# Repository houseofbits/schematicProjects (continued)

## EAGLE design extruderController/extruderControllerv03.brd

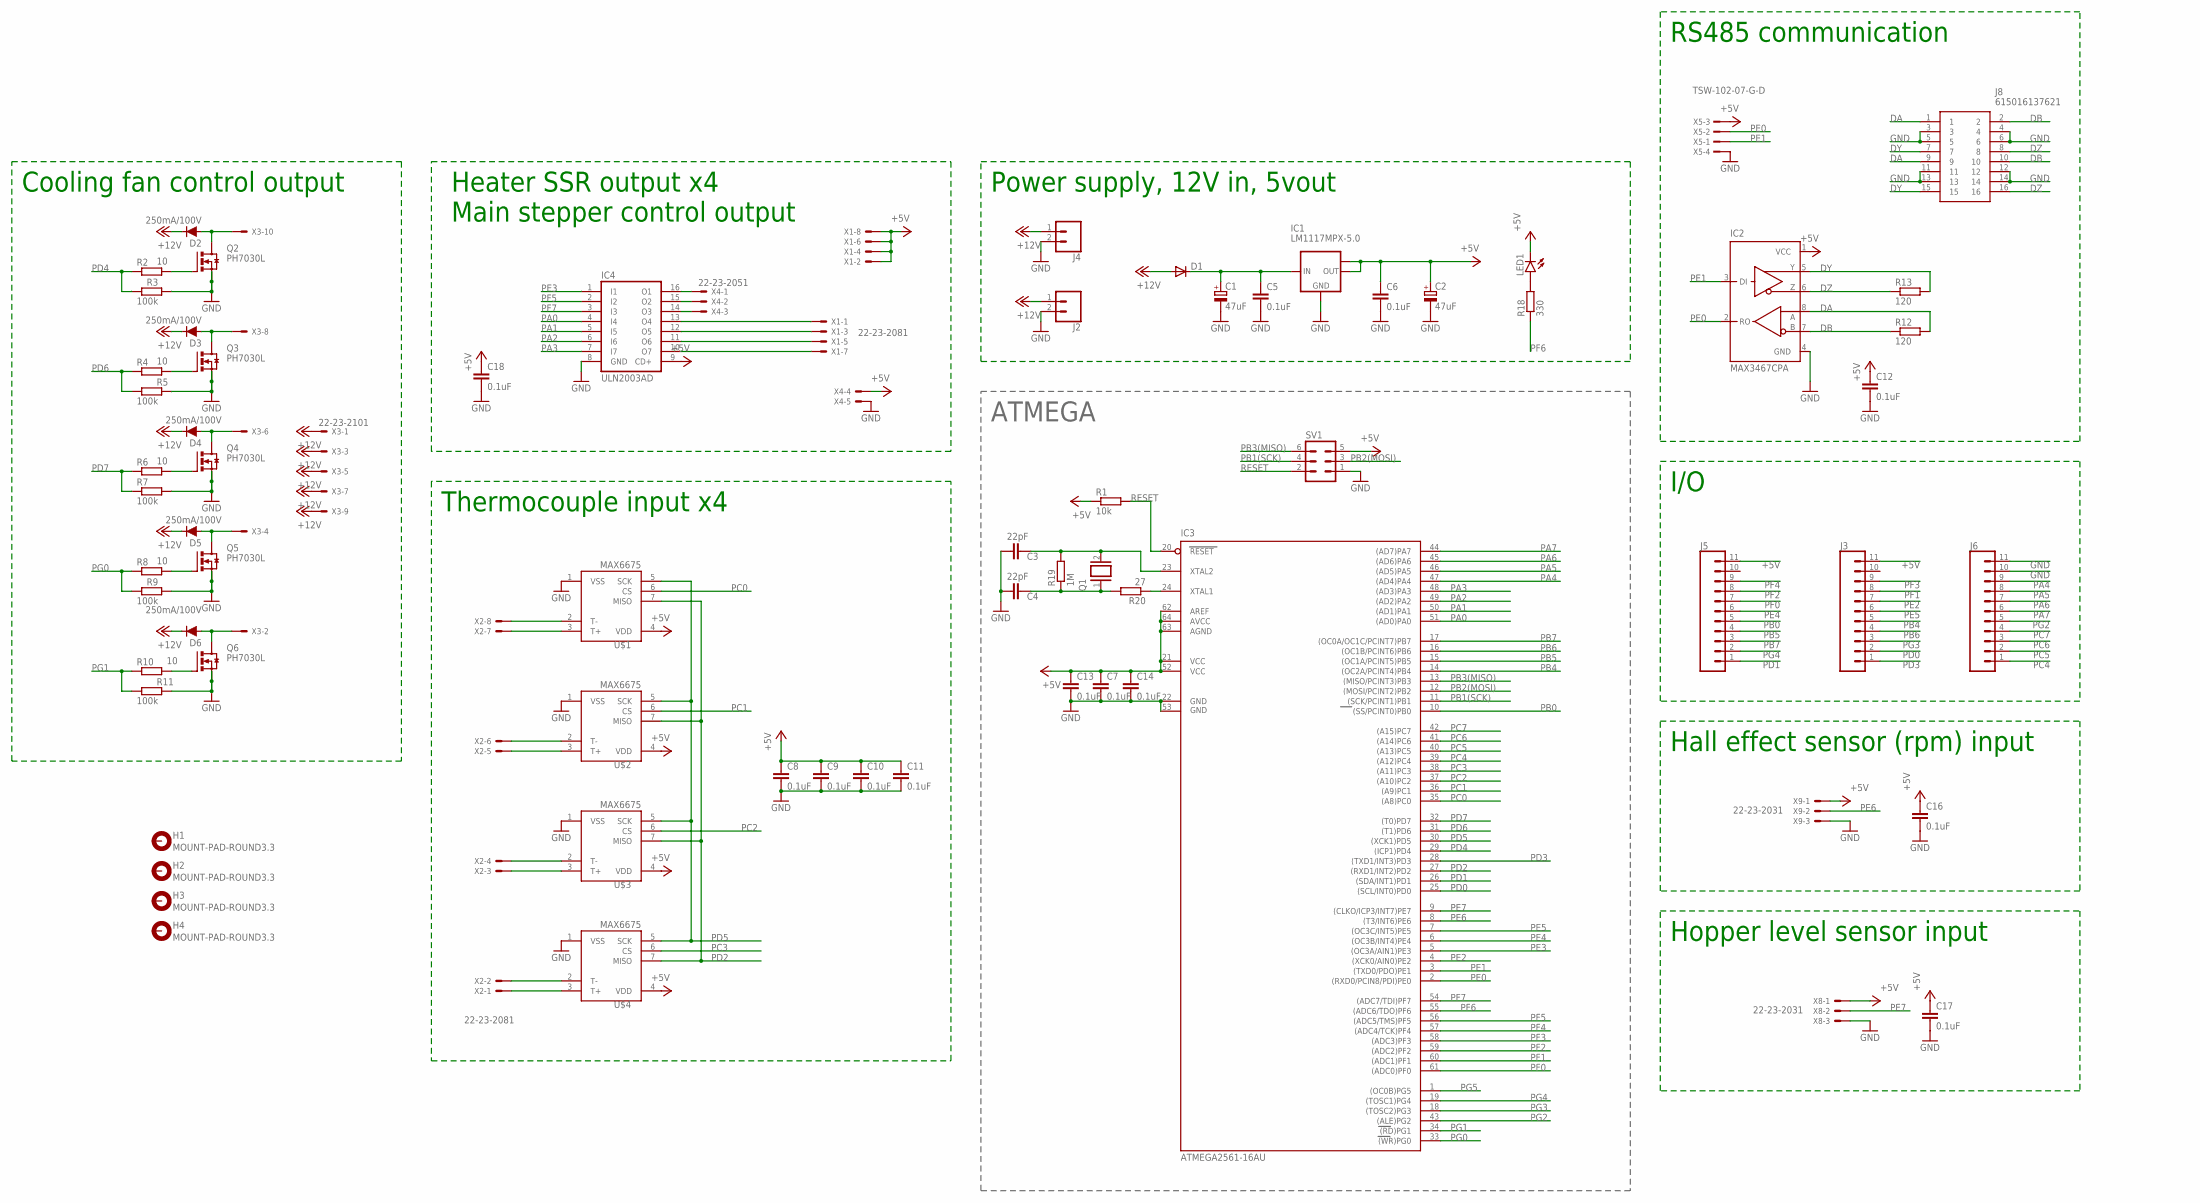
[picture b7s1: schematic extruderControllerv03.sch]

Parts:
C1, C2: 47uF; PANASONIC_D
C3, C4: 22pF; C0603
C5, C6, C7, C8, C9, C10, C11, C12, C13, C14, C16, C17, C18: 0.1uF; C0603
D1: DIODE-SMB; SMB
D2, D3, D4, D5, D6: 250mA/100V; SOD-323
H1, H2, H3, H4: MOUNT-PAD-ROUND3.3; 3,3-PAD
IC1: LM1117MPX-5.0; SOT223
IC2: MAX3467CPA; SO08
IC3: ATMEGA2561-16AU; TQFP64
IC4: ULN2003AD; SO16
J2, J4: CONN_023.5MM; SCREWTERMINAL-3.5MM-2
J3, J5, J6: CONN_11; 1X11
J8: 615016137621; WR-MJ
LED1: LEDSML1206; SML1206
Q1: XTAL/S; QS
Q2, Q3, Q4, Q5, Q6: PH7030L; SOT669
R1: 10k; R0805
R2, R4, R6, R8, R10: 10; R0805
R3, R5, R7, R9, R11: 100k; R0805
R12, R13: 120; R1210
R18: 330; R0805
R19: 1M; R0805
R20: 27; R0805
SV1: MA03-2
U$1, U$2, U$3, U$4: MAX6675; SO08-MAX6675
X1, X2: 22-23-2081
X3: 22-23-2101
X4: 22-23-2051
X5: TSW-102-07-G-D; TSW-102-XX-G-D
X8, X9: 22-23-2031

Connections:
+5V: C2.+, C6.1, C7.1, C8.1, C9.1, C10.1, C11.1, C12.1, C13.1, C14.1, C16.1, C17.1, C18.1, IC1.2 (OUT), IC1.TAB (OUT1), IC2.1 (VCC), IC3.21 (VCC), IC3.52 (VCC1), IC3.62 (AREF), IC3.63 (AGND), IC3.64 (AVCC), IC4.9 (CD+), J3.11, J5.11, LED1.C, R1.1, SV1.5, U$1.4 (VDD), U$2.4 (VDD), U$3.4 (VDD), U$4.4 (VDD), X1.2, X1.4, X1.6, X1.8, X4.4, X5.3, X8.1, X9.1
+12V: D1.A, D2.C, D3.C, D4.C, D5.C, D6.C, J2.1, J4.1, X3.1, X3.3, X3.5, X3.7, X3.9
DA: IC2.8 (A), J8.1, J8.9, R12.2
DB: IC2.7 (B), J8.2, J8.10, R12.1
DY: IC2.5 (Y), J8.7, J8.15, R13.2
DZ: IC2.6 (Z), J8.8, J8.16, R13.1
GND: C1.-, C2.-, C3.2, C4.2, C5.2, C6.2, C7.2, C8.2, C9.2, C10.2, C11.2, C12.2, C13.2, C14.2, C16.2, C17.2, C18.2, IC1.1 (GND), IC2.4 (GND), IC3.22 (GND), IC3.53 (GND1), IC4.8 (GND), J2.2, J4.2, J6.10, J6.11, J8.3, J8.4, J8.5, J8.6, J8.11, J8.12, J8.13, J8.14, Q2.1 (S), Q2.2 (S), Q2.3 (S), Q3.1 (S), Q3.2 (S), Q3.3 (S), Q4.1 (S), Q4.2 (S), Q4.3 (S), Q5.1 (S), Q5.2 (S), Q5.3 (S), Q6.1 (S), Q6.2 (S), Q6.3 (S), R3.2, R5.2, R7.2, R9.2, R11.2, SV1.1, U$1.1 (VSS), U$2.1 (VSS), U$3.1 (VSS), U$4.1 (VSS), X4.5, X5.4, X8.3, X9.3
unnamed: Q2.4 (G), R2.2
unnamed: U$1.2 (T-), X2.8
unnamed: U$1.3 (T+), X2.7
unnamed: U$2.2 (T-), X2.6
unnamed: U$2.3 (T+), X2.5
unnamed: U$3.2 (T-), X2.4
unnamed: U$3.3 (T+), X2.3
unnamed: U$4.2 (T-), X2.2
unnamed: U$4.3 (T+), X2.1
unnamed: IC4.12 (O5), X1.3
unnamed: IC4.11 (O6), X1.5
unnamed: IC4.10 (O7), X1.7
unnamed: IC4.15 (O2), X4.2
unnamed: C1.+, C5.1, D1.C, IC1.3 (IN)
unnamed: C3.1, IC3.23 (XTAL2), Q1.2, R19.2
unnamed: C4.1, Q1.1, R19.1, R20.2
unnamed: IC4.14 (O3), X4.3
unnamed: D2.A, Q2.MB (D), X3.10
unnamed: Q3.4 (G), R4.2
unnamed: D3.A, Q3.MB (D), X3.8
unnamed: Q4.4 (G), R6.2
unnamed: IC4.16 (O1), X4.1
unnamed: D4.A, Q4.MB (D), X3.6
unnamed: Q5.4 (G), R8.2
unnamed: IC4.13 (O4), X1.1
unnamed: D5.A, Q5.MB (D), X3.4
unnamed: Q6.4 (G), R10.2
unnamed: D6.A, Q6.MB (D), X3.2
unnamed: IC3.24 (XTAL1), R20.1
unnamed: LED1.A, R18.2
PA0: IC3.51 ((AD0)PA0), IC4.4 (I4)
PA1: IC3.50 ((AD1)PA1), IC4.5 (I5)
PA2: IC3.49 ((AD2)PA2), IC4.6 (I6)
PA3: IC3.48 ((AD3)PA3), IC4.7 (I7)
PA4: IC3.47 ((AD4)PA4), J6.9
PA5: IC3.46 ((AD5)PA5), J6.8
PA6: IC3.45 ((AD6)PA6), J6.7
PA7: IC3.44 ((AD7)PA7), J6.6
PB0: IC3.10 ((SS/PCINT0)PB0), J5.5
PB1(SCK): IC3.11 ((SCK/PCINT1)PB1), SV1.4
PB2(MOSI): IC3.12 ((MOSI/PCINT2)PB2), SV1.3
PB3(MISO): IC3.13 ((MISO/PCINT3)PB3), SV1.6
PB4: IC3.14 ((OC2A/PCINT4)PB4), J3.5
PB5: IC3.15 ((OC1A/PCINT5)PB5), J5.4
PB6: IC3.16 ((OC1B/PCINT6)PB6), J3.4
PB7: IC3.17 ((OC0A/OC1C/PCINT7)PB7), J5.3
PC0: IC3.35 ((A8)PC0), U$1.6 (CS)
PC1: IC3.36 ((A9)PC1), U$2.6 (CS)
PC2: IC3.37 ((A10)PC2), U$3.6 (CS)
PC3: IC3.38 ((A11)PC3), U$4.6 (CS)
PC4: IC3.39 ((A12)PC4), J6.1
PC5: IC3.40 ((A13)PC5), J6.2
PC6: IC3.41 ((A14)PC6), J6.3
PC7: IC3.42 ((A15)PC7), J6.4
PD0: IC3.25 ((SCL/INT0)PD0), J3.2
PD1: IC3.26 ((SDA/INT1)PD1), J5.1
PD2: IC3.27 ((RXD1/INT2)PD2), U$1.7 (MISO), U$2.7 (MISO), U$3.7 (MISO), U$4.7 (MISO)
PD3: IC3.28 ((TXD1/INT3)PD3), J3.1
PD4: IC3.29 ((ICP1)PD4), R2.1, R3.1
PD5: IC3.30 ((XCK1)PD5), U$1.5 (SCK), U$2.5 (SCK), U$3.5 (SCK), U$4.5 (SCK)
PD6: IC3.31 ((T1)PD6), R4.1, R5.1
PD7: IC3.32 ((T0)PD7), R6.1, R7.1
PE0: IC2.2 (RO), IC3.2 ((RXD0/PCIN8/PDI)PE0), X5.2
PE1: IC2.3 (DI), IC3.3 ((TXD0/PDO)PE1), X5.1
PE2: IC3.4 ((XCK0/AIN0)PE2), J3.7
PE3: IC3.5 ((OC3A/AIN1)PE3), IC4.1 (I1)
PE4: IC3.6 ((OC3B/INT4)PE4), J5.6
PE5: IC3.7 ((OC3C/INT5)PE5), J3.6
PE6: IC3.8 ((T3/INT6)PE6), X9.2
PE7: IC3.9 ((CLKO/ICP3/INT7)PE7), X8.2
PF0: IC3.61 ((ADC0)PF0), J5.7
PF1: IC3.60 ((ADC1)PF1), J3.8
PF2: IC3.59 ((ADC2)PF2), J5.8
PF3: IC3.58 ((ADC3)PF3), J3.9
PF4: IC3.57 ((ADC4/TCK)PF4), J5.9
PF5: IC3.56 ((ADC5/TMS)PF5), IC4.2 (I2)
PF6: IC3.55 ((ADC6/TDO)PF6), R18.1
PF7: IC3.54 ((ADC7/TDI)PF7), IC4.3 (I3)
PG0: IC3.33 ((WR)PG0), R8.1, R9.1
PG1: IC3.34 ((RD)PG1), R10.1, R11.1
PG2: IC3.43 ((ALE)PG2), J6.5
PG3: IC3.18 ((TOSC2)PG3), J3.3
PG4: IC3.19 ((TOSC1)PG4), J5.2
PG5: IC3.1 ((OC0B)PG5)
RESET: IC3.20 (RESET), R1.2, SV1.2

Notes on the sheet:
Power supply, 12V in, 5vout
ATMEGA
Thermocouple input x4
Heater SSR output x4
Main stepper control output
Hall effect sensor (rpm) input
RS485 communication
Hopper level sensor input
Cooling fan control output
I/O

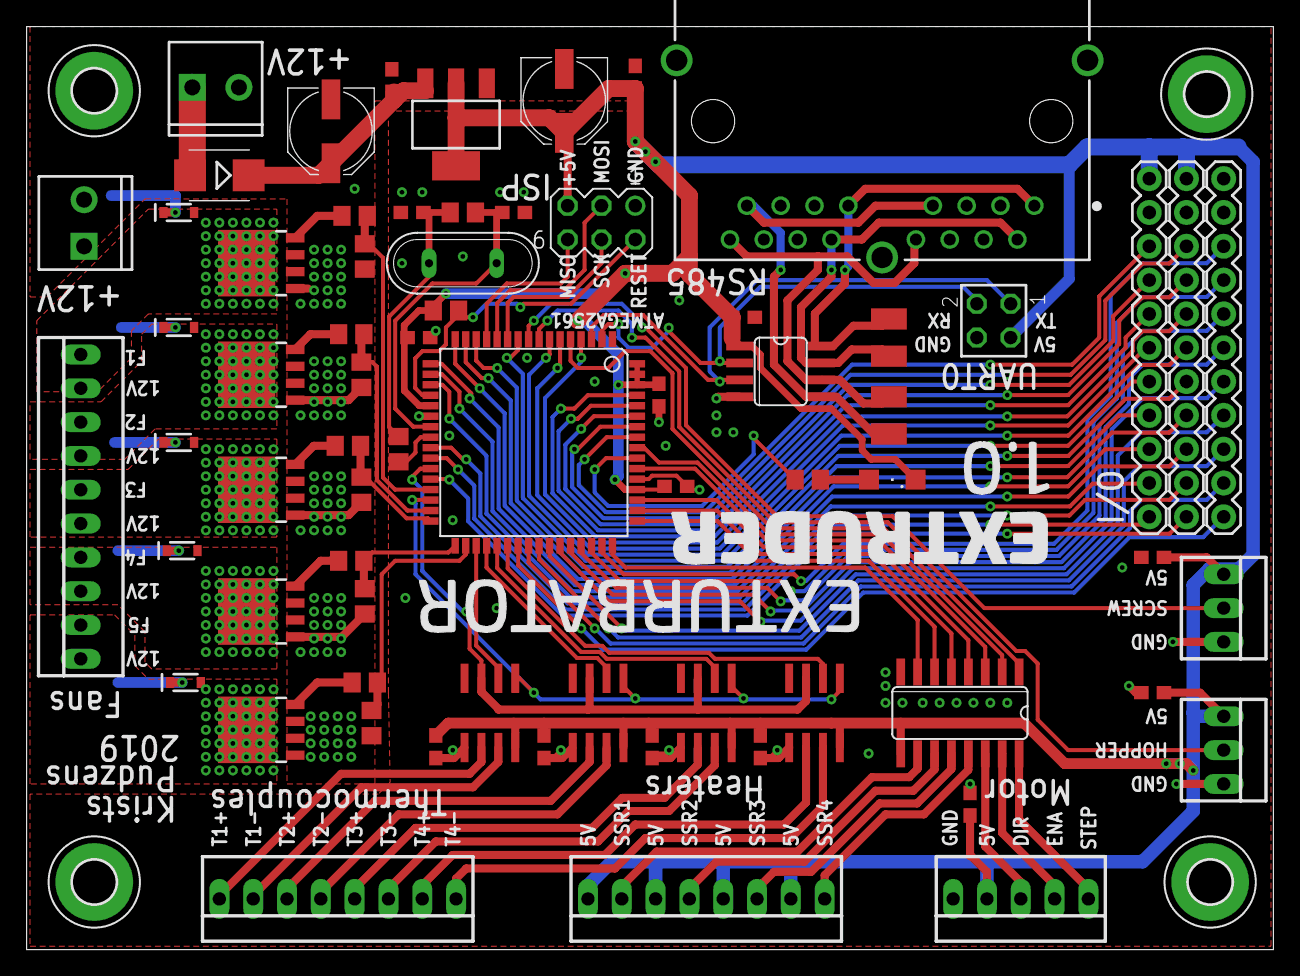
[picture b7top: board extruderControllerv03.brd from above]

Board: 2 copper layers, 93.7 x 69.3 mm, 72 parts (0 on the bottom side), 91 nets.

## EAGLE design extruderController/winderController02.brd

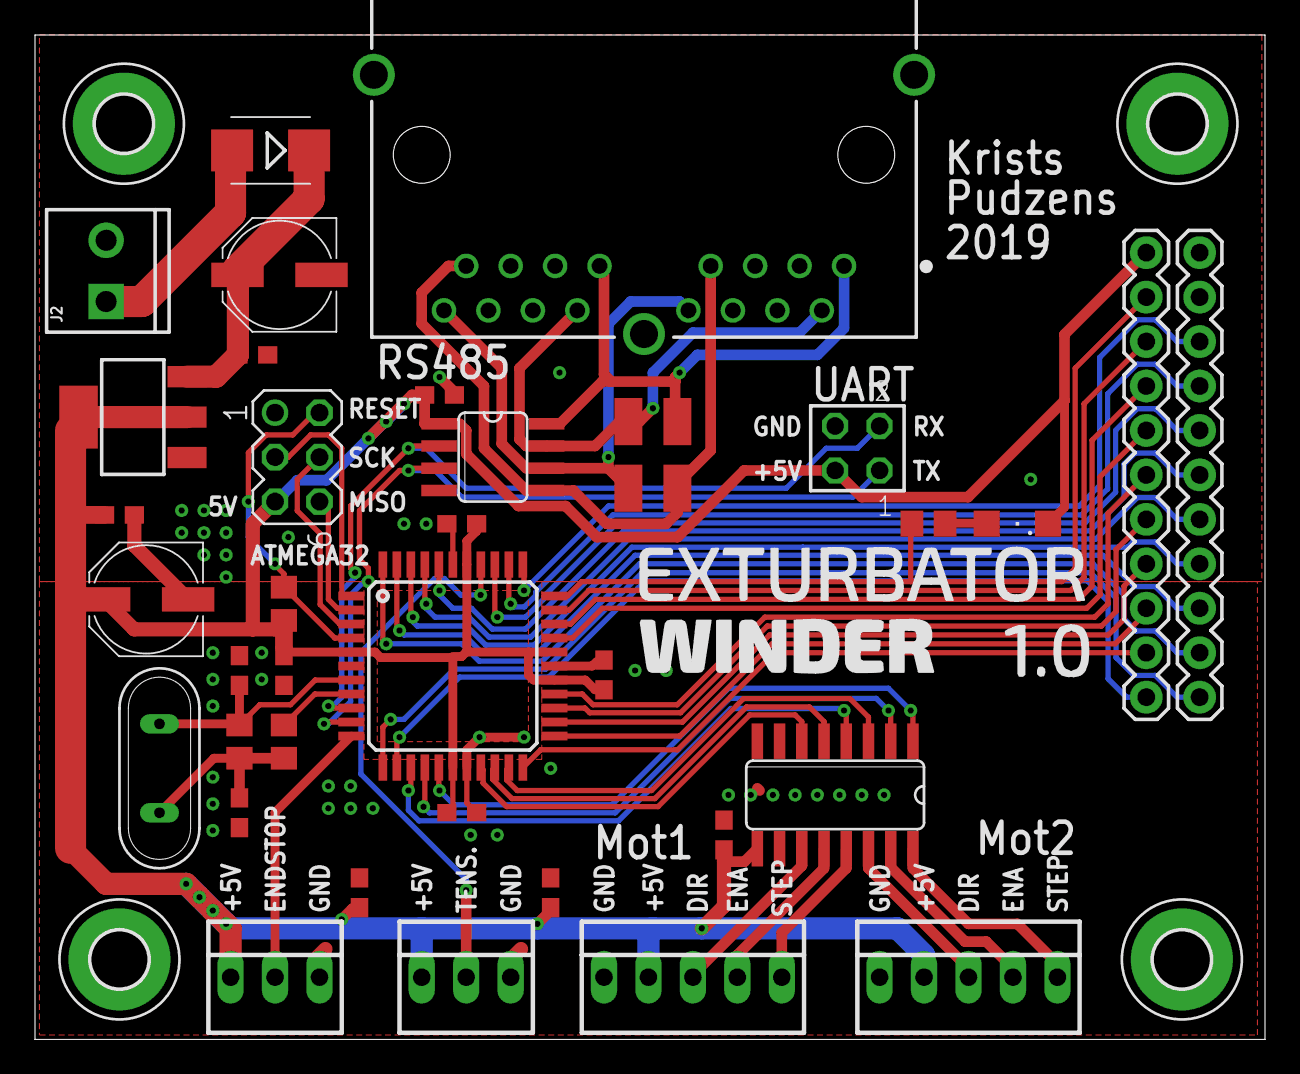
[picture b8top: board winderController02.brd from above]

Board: 2 copper layers, 70.3 x 57.4 mm, 41 parts (0 on the bottom side), 51 nets.

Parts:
C1, C2: 47uF; PANASONIC_D
C3, C4: C0603
C5, C6, C7, C8, C12, C13, C14, C16, C17, C18: 0.1uF; C0603
D1: SMB
H1, H2, H3, H4: MOUNT-PAD-ROUND3.3; 3,3-PAD
IC1: LM1117MPX-5.0; SOT223
IC2: MAX3467CPA; SO08
IC3: MEGA32-A; TQFP44
IC4: ULN2003AD; SO16
J2: SCREWTERMINAL-3.5MM-2
J3, J5: 1X11
J8: 615016137621; WR-MJ
LED1: SML1206
Q1: QS
R1: 10k; R0805
R12, R13: 120; R1210
R18: 330; R0805
R19: 1M; R0805
R20: 27; R0805
SV1: MA03-2
X1, X2: 22-23-2051
X5: TSW-102-07-G-D; TSW-102-XX-G-D
X8, X9: 22-23-2031

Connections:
+5V: C2.+, C6.1, C7.1, C8.1, C12.1, C13.1, C14.1, C16.1, C17.1, C18.1, IC1.2, IC1.TAB, IC2.1, IC3.5, IC3.17, IC3.27, IC3.29, IC3.38, IC4.9, J3.11, LED1.C, R1.1, SV1.5, X1.2, X2.2, X5.3, X8.1, X9.1
+12V: D1.A, J2.1
DA: IC2.8, J8.1, J8.9, R12.2
DB: IC2.7, J8.2, J8.10, R12.1
DY: IC2.5, J8.7, J8.15, R13.2
DZ: IC2.6, J8.8, J8.16, R13.1
GND: C1.-, C2.-, C3.2, C4.2, C5.2, C6.2, C7.2, C8.2, C12.2, C13.2, C14.2, C16.2, C17.2, C18.2, IC1.1, IC2.4, IC3.6, IC3.18, IC3.28, IC3.39, IC4.7, IC4.8, J2.2, J5.10, J5.11, J8.3, J8.4, J8.5, J8.6, J8.11, J8.12, J8.13, J8.14, SV1.1, X1.1, X2.1, X5.4, X8.3, X9.3
unnamed: IC4.11, X1.3
unnamed: IC4.12, X1.4
unnamed: IC4.13, X1.5
unnamed: IC4.14, X2.3
unnamed: C1.+, C5.1, D1.C, IC1.3
unnamed: C3.1, IC3.7, Q1.2, R19.2
unnamed: C4.1, Q1.1, R19.1, R20.2
unnamed: IC4.15, X2.4
unnamed: IC4.16, X2.5
unnamed: IC3.8, R20.1
unnamed: LED1.A, R18.2
PA0: IC3.37, X8.2
PA1: IC3.36, J5.7
PA2: IC3.35, J5.8
PA3: IC3.34, J5.9
PA4: IC3.33, J3.10, R18.1
PA5: IC3.32, J3.9
PA6: IC3.31, J3.8
PA7: IC3.30, J3.7
PB0: IC3.40, J5.6
PB1: IC3.41, J5.5
PB2: IC3.42, J5.4
PB3: IC3.43, J5.3
PB4: IC3.44, J5.2
PB5(MOSI): IC3.1, SV1.3
PB6(MISO): IC3.2, SV1.6
PB7(SCK): IC3.3, SV1.4
PC0: IC3.19, IC4.6
PC1: IC3.20, IC4.5
PC2: IC3.21, IC4.3
PC3: IC3.22, J3.2
PC4: IC3.23, J3.3
PC5: IC3.24, J3.4
PC6: IC3.25, J3.5
PC7: IC3.26, J3.6
PD0: IC2.2, IC3.9, X5.2
PD1: IC2.3, IC3.10, X5.1
PD2: IC3.11, X9.2
PD3: IC3.12, J5.1
PD4: IC3.13, J3.1
PD5: IC3.14, IC4.4
PD6: IC3.15, IC4.2
PD7: IC3.16, IC4.1
RESET: IC3.4, R1.2, SV1.2
